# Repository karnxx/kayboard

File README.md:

# split keyboard - kayboard
https://a360.co/4jg0f7l
basically a keyboard, it can split into 3, which is a left side, a right side and a middle calculator side. so these keyboards can also join together to make 1 big keyboard via rails. 

## hardware
- uses 3  XIAO-nRF52840-SMD, one for each keyboard part. and also uses cherry mx switches.
- https://docs.google.com/spreadsheets/d/1L9tUZh8eFOhgZV8CGI-1AN47H67KgHnQl9KeM_NllnM/edit?usp=sharing

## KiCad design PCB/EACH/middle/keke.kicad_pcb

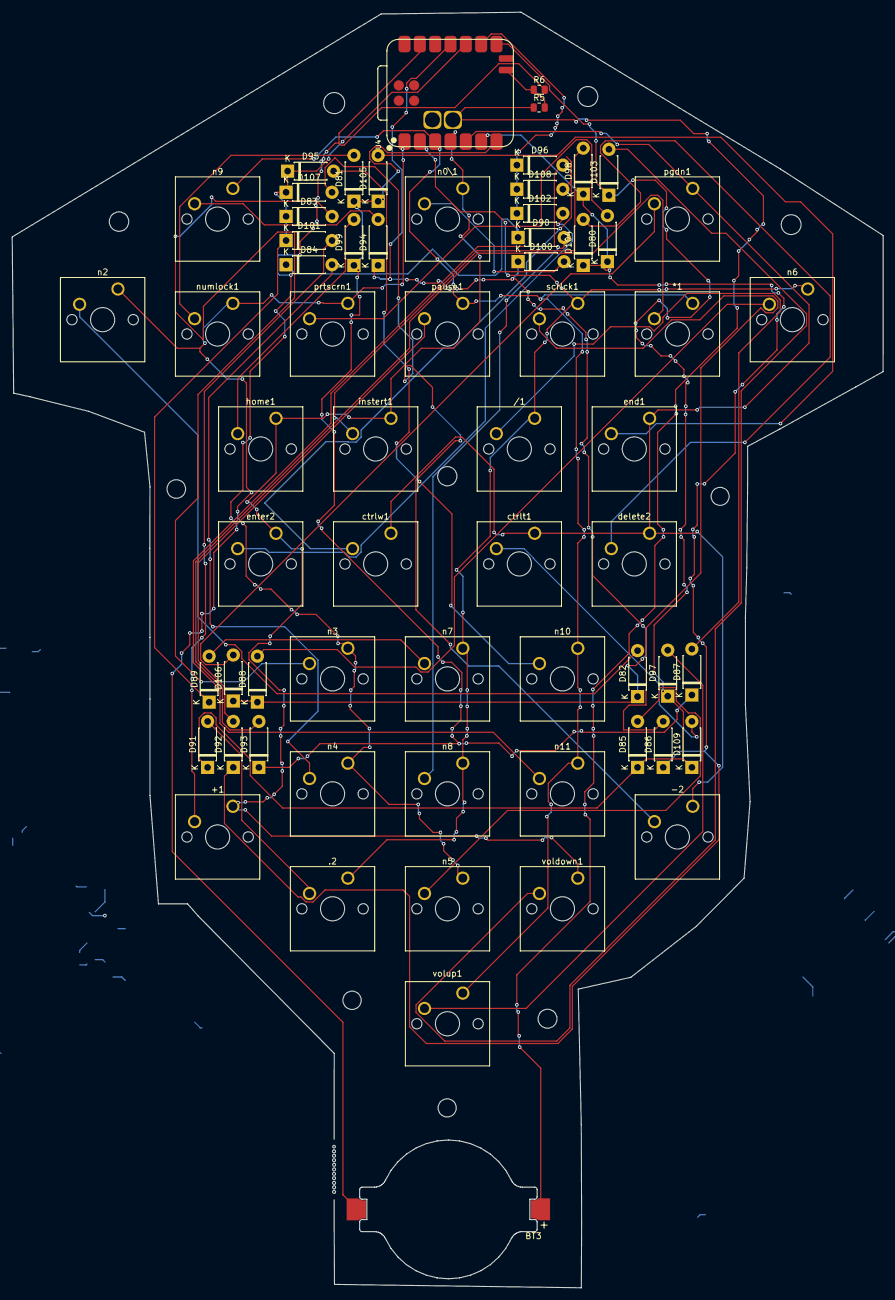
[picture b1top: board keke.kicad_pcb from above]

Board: 2 copper layers, 144.3 x 211.4 mm, 64 parts (0 on the bottom side), 44 nets.

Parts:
*1: SW_Push; SW_Cherry_MX_1.00u_PCB
+1: SW_Push; SW_Cherry_MX_1.00u_PCB
-2: SW_Push; SW_Cherry_MX_1.00u_PCB
.2: SW_Push; SW_Cherry_MX_1.00u_PCB
/1: SW_Push; SW_Cherry_MX_1.00u_PCB
BT3: Battery; BatteryHolder_Keystone_1057_1x2032
D80, D81, D82, D83, D84, D85, D86, D87, D88, D89, D90, D91, D92, D93, D94, D95, D96, D97, D98, D99, D100, D101, D102, D103, D104, D105, D106, D107, D108, D109: D; D_DO-41_SOD81_P7.62mm_Horizontal
R5, R6: R; R_0805_2012Metric
U4: XIAO-nRF52840-SMD; modified-XIAO-nRF52840-SMD
ctrlt1: SW_Push; SW_Cherry_MX_1.00u_PCB
ctrlw1: SW_Push; SW_Cherry_MX_1.00u_PCB
delete2: SW_Push; SW_Cherry_MX_1.00u_PCB
end1: SW_Push; SW_Cherry_MX_1.00u_PCB
enter2: SW_Push; SW_Cherry_MX_1.00u_PCB
home1: SW_Push; SW_Cherry_MX_1.00u_PCB
instert1: SW_Push; SW_Cherry_MX_1.00u_PCB
n0\1, n2, n3, n4, n5, n6, n7, n8, n9, n10, n11: SW_Push; SW_Cherry_MX_1.00u_PCB
numlock1: SW_Push; SW_Cherry_MX_1.00u_PCB
pause1: SW_Push; SW_Cherry_MX_1.00u_PCB
pgdn1: SW_Push; SW_Cherry_MX_1.00u_PCB
prtscrn1: SW_Push; SW_Cherry_MX_1.00u_PCB
scrlck1: SW_Push; SW_Cherry_MX_1.00u_PCB
voldown1: SW_Push; SW_Cherry_MX_1.00u_PCB
volup1: SW_Push; SW_Cherry_MX_1.00u_PCB

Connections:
/middle/VBAT3: BT3.1 (+), R5.1, U4.15 (BAT)
/middle/c0: U4.1 (P0.02_A0_D0), n2.1, n3.1, n4.1, n5.1, numlock1.1, prtscrn1.1
/middle/c1: .2.1, /1.1, U4.2 (P0.03_A1_D1), n6.1, n7.1, n8.1, scrlck1.1
/middle/c2: *1.1, U4.3 (P0.28_A2_D2), n9.1, n10.1, n11.1, pause1.1, volup1.1
/middle/c3: +1.1, U4.4 (P0.29_A3_D3), enter2.1, home1.1, instert1.1, n0\1.1, voldown1.1
/middle/c4: -2.1, U4.5 (P0.04_A4_D4_SDA), ctrlt1.1, ctrlw1.1, delete2.1, end1.1, pgdn1.1
/middle/pin: R5.2, R6.1, U4.17 (NFC1)
/middle/r0: D80.1 (K), D86.1 (K), D92.1 (K), D98.1 (K), D104.1 (K), U4.6 (P0.05_A5_D5_SCL)
/middle/r1: D81.1 (K), D87.1 (K), D93.1 (K), D99.1 (K), D105.1 (K), U4.7 (P1.11_D6_TX)
/middle/r2: D82.1 (K), D88.1 (K), D94.1 (K), D100.1 (K), D106.1 (K), U4.11 (P1.15_D10_MOSI)
/middle/r3: D83.1 (K), D89.1 (K), D95.1 (K), D101.1 (K), D107.1 (K), U4.10 (P1.14_D9_MISO)
/middle/r4: D84.1 (K), D90.1 (K), D96.1 (K), D102.1 (K), D108.1 (K), U4.9 (P1.13_D8_SCK)
/middle/r5: D85.1 (K), D91.1 (K), D97.1 (K), D103.1 (K), D109.1 (K), U4.8 (P1.12_D7_RX)
GND3: BT3.2 (-), R6.2, U4.13 (GND)
unnamed: D80.2 (A), prtscrn1.2
unnamed: D81.2 (A), numlock1.2
unnamed: D82.2 (A), n2.2
unnamed: D83.2 (A), n3.2
unnamed: D84.2 (A), n4.2
unnamed: D85.2 (A), n5.2
unnamed: D86.2 (A), scrlck1.2
unnamed: /1.2, D87.2 (A)
unnamed: D88.2 (A), n6.2
unnamed: D89.2 (A), n7.2
unnamed: D90.2 (A), n8.2
unnamed: .2.2, D91.2 (A)
unnamed: D92.2 (A), pause1.2
unnamed: *1.2, D93.2 (A)
unnamed: D94.2 (A), n9.2
unnamed: D95.2 (A), n10.2
unnamed: D96.2 (A), n11.2
unnamed: D97.2 (A), volup1.2
unnamed: D98.2 (A), instert1.2
unnamed: D99.2 (A), home1.2
unnamed: D100.2 (A), n0\1.2
unnamed: +1.2, D101.2 (A)
unnamed: D102.2 (A), enter2.2
unnamed: D103.2 (A), voldown1.2
unnamed: D104.2 (A), delete2.2
unnamed: D105.2 (A), end1.2
unnamed: D106.2 (A), pgdn1.2
unnamed: -2.2, D107.2 (A)
unnamed: D108.2 (A), ctrlw1.2
unnamed: D109.2 (A), ctrlt1.2

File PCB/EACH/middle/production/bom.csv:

Designator,Footprint,Quantity,Value,LCSC Part #
"*1, +1, -2, .2, /1, CTRLT1, CTRLW1, DELETE2, END1, ENTER2, HOME1, INSTERT1, N0\1, N10, N11, N2, N3, N4, N5, N6, N7, N8, N9, NUMLOCK1, PAUSE1, PGDN1, PRTSCRN1, SCRLCK1, VOLDOWN1, VOLUP1",SW_Cherry_MX_1.00u_PCB,30,SW_Push,
BT3,BatteryHolder_Keystone_1057_1x2032,1,Battery,
"D100, D101, D102, D103, D104, D105, D106, D107, D108, D109, D80, D81, D82, D83, D84, D85, D86, D87, D88, D89, D90, D91, D92, D93, D94, D95, D96, D97, D98, D99",D_DO-41_SOD81_P7.62mm_Horizontal,30,D,
"R5, R6",0805,2,R,
U4,modified-XIAO-nRF52840-SMD,1,XIAO-nRF52840-SMD,

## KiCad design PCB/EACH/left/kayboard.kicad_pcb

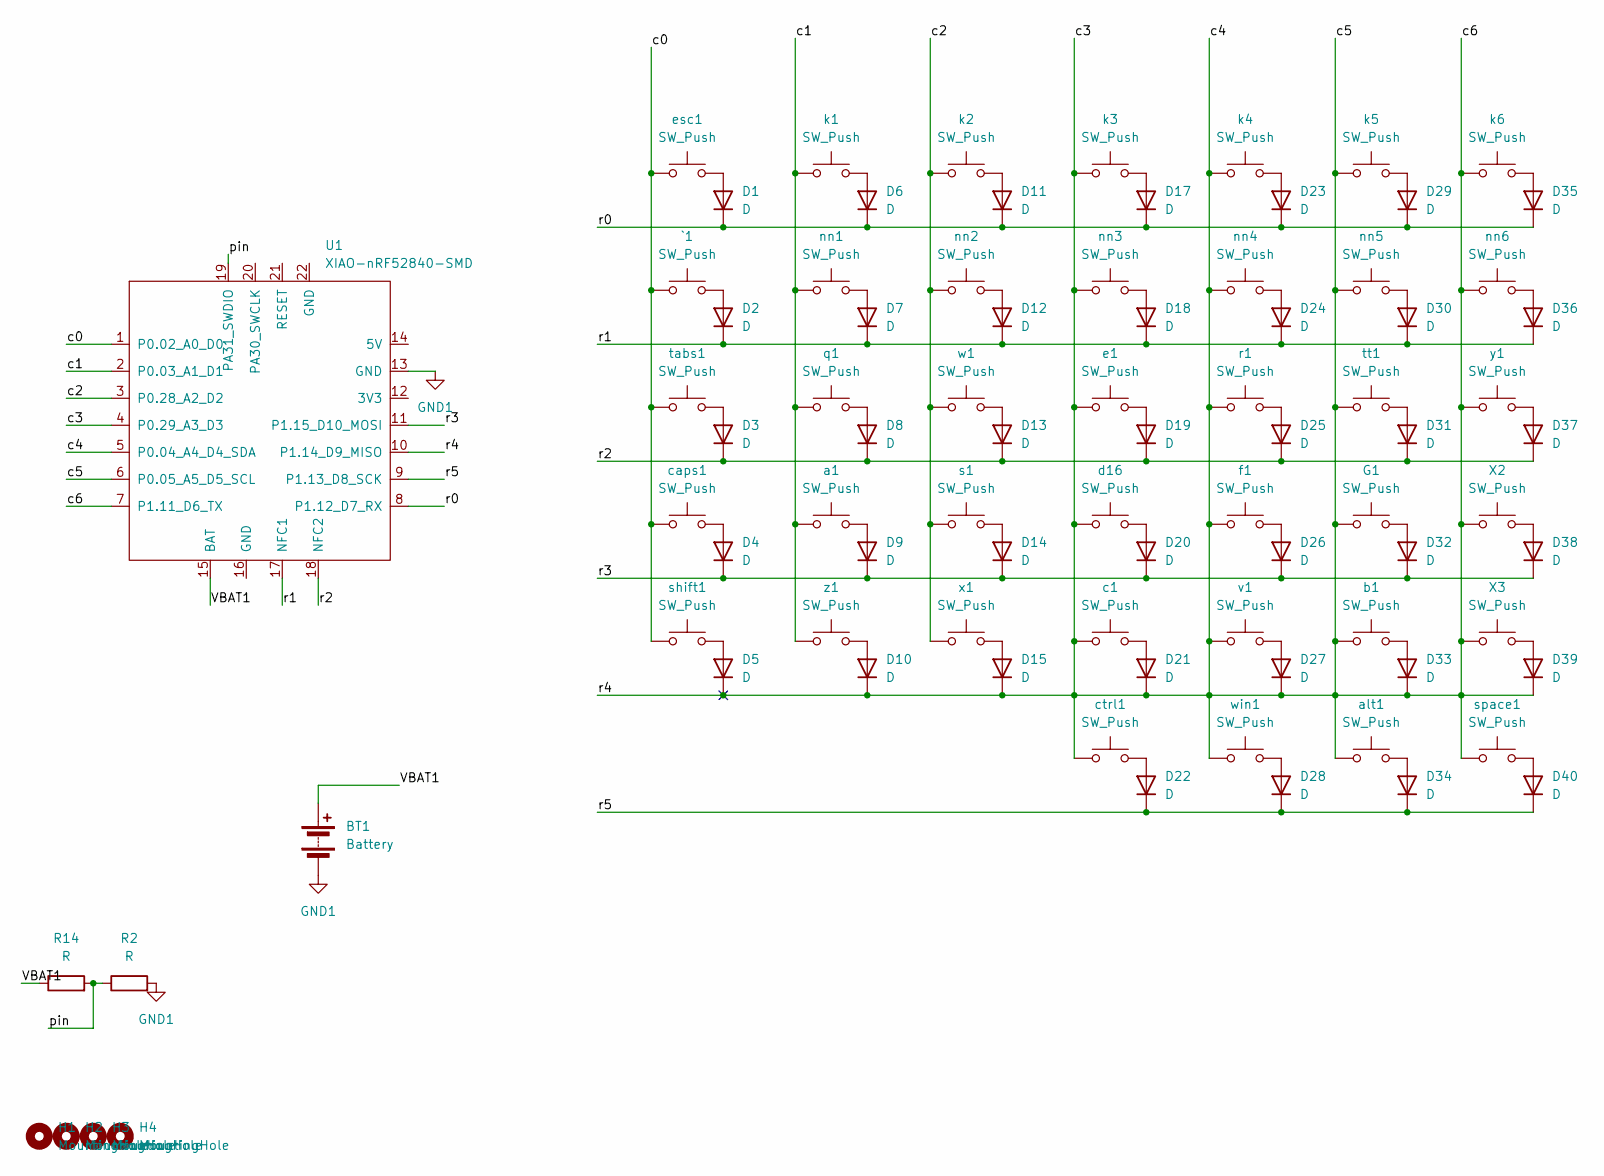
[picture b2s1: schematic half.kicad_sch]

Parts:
BT1: Battery; BatteryHolder_Keystone_1057_1x2032
D1, D2, D3, D4, D5, D6, D7, D8, D9, D10, D11, D12, D13, D14, D15, D17, D18, D19, D20, D21, D22, D23, D24, D25, D26, D27, D28, D29, D30, D31, D32, D33, D34, D35, D36, D37, D38, D39, D40: D; D_DO-41_SOD81_P7.62mm_Horizontal
G1: SW_Push; SW_Cherry_MX_1.00u_PCB
H1, H2, H3, H4: MountingHole; mouse-bite-5mm-slot
R2, R14: R; R_0805_2012Metric
U1: XIAO-nRF52840-SMD; modified-XIAO-nRF52840-SMD
X2, X3: SW_Push; SW_Cherry_MX_1.00u_PCB
`1: SW_Push; SW_Cherry_MX_1.00u_PCB
a1: SW_Push; SW_Cherry_MX_1.00u_PCB
alt1: SW_Push; SW_Cherry_MX_1.00u_PCB
b1: SW_Push; SW_Cherry_MX_1.00u_PCB
c1: SW_Push; SW_Cherry_MX_1.00u_PCB
caps1: SW_Push; SW_Cherry_MX_1.00u_PCB
ctrl1: SW_Push; SW_Cherry_MX_1.00u_PCB
d16: SW_Push; SW_Cherry_MX_1.00u_PCB
e1: SW_Push; SW_Cherry_MX_1.00u_PCB
esc1: SW_Push; SW_Cherry_MX_1.00u_PCB
f1: SW_Push; SW_Cherry_MX_1.00u_PCB
k1, k2, k3, k4, k5, k6: SW_Push; SW_Cherry_MX_1.00u_PCB
nn1, nn2, nn3, nn4, nn5, nn6: SW_Push; SW_Cherry_MX_1.00u_PCB
q1: SW_Push; SW_Cherry_MX_1.00u_PCB
r1: SW_Push; SW_Cherry_MX_1.00u_PCB
s1: SW_Push; SW_Cherry_MX_1.00u_PCB
shift1: SW_Push; SW_Cherry_MX_1.00u_PCB
space1: SW_Push; SW_Cherry_MX_1.00u_PCB
tabs1: SW_Push; SW_Cherry_MX_1.00u_PCB
tt1: SW_Push; SW_Cherry_MX_1.00u_PCB
v1: SW_Push; SW_Cherry_MX_1.00u_PCB
w1: SW_Push; SW_Cherry_MX_1.00u_PCB
win1: SW_Push; SW_Cherry_MX_1.00u_PCB
x1: SW_Push; SW_Cherry_MX_1.00u_PCB
y1: SW_Push; SW_Cherry_MX_1.00u_PCB
z1: SW_Push; SW_Cherry_MX_1.00u_PCB

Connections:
/left/VBAT1: BT1.1 (+), R14.1, U1.15 (BAT)
/left/c0: U1.1 (P0.02_A0_D0), `1.1, caps1.1, esc1.1, shift1.1, tabs1.1
/left/c1: U1.2 (P0.03_A1_D1), a1.1, k1.1, nn1.1, q1.1, z1.1
/left/c2: U1.3 (P0.28_A2_D2), k2.1, nn2.1, s1.1, w1.1, x1.1
/left/c3: D5.1 (K), D10.1 (K), D15.1 (K), D21.1 (K), D27.1 (K), D33.1 (K), D39.1 (K), G1.1, U1.4 (P0.29_A3_D3), U1.5 (P0.04_A4_D4_SDA), U1.6 (P0.05_A5_D5_SCL), U1.7 (P1.11_D6_TX), U1.10 (P1.14_D9_MISO), X2.1, X3.1, alt1.1, b1.1, c1.1, ctrl1.1, d16.1, e1.1, f1.1, k3.1, k4.1, k5.1, k6.1, nn3.1, nn4.1, nn5.1, nn6.1, r1.1, space1.1, tt1.1, v1.1, win1.1, y1.1
/left/pin: R2.1, R14.2, U1.19 (PA31_SWDIO)
/left/r0: D1.1 (K), D6.1 (K), D11.1 (K), D17.1 (K), D23.1 (K), D29.1 (K), D35.1 (K), U1.8 (P1.12_D7_RX)
/left/r1: D2.1 (K), D7.1 (K), D12.1 (K), D18.1 (K), D24.1 (K), D30.1 (K), D36.1 (K), U1.17 (NFC1)
/left/r2: D3.1 (K), D8.1 (K), D13.1 (K), D19.1 (K), D25.1 (K), D31.1 (K), D37.1 (K), U1.18 (NFC2)
/left/r3: D4.1 (K), D9.1 (K), D14.1 (K), D20.1 (K), D26.1 (K), D32.1 (K), D38.1 (K), U1.11 (P1.15_D10_MOSI)
/left/r5: D22.1 (K), D28.1 (K), D34.1 (K), D40.1 (K), U1.9 (P1.13_D8_SCK)
GND1: BT1.2 (-), R2.2, U1.13 (GND)
unnamed: D1.2 (A), esc1.2
unnamed: D2.2 (A), `1.2
unnamed: D3.2 (A), tabs1.2
unnamed: D4.2 (A), caps1.2
unnamed: D5.2 (A), shift1.2
unnamed: D6.2 (A), k1.2
unnamed: D7.2 (A), nn1.2
unnamed: D8.2 (A), q1.2
unnamed: D9.2 (A), a1.2
unnamed: D10.2 (A), z1.2
unnamed: D11.2 (A), k2.2
unnamed: D12.2 (A), nn2.2
unnamed: D13.2 (A), w1.2
unnamed: D14.2 (A), s1.2
unnamed: D15.2 (A), x1.2
unnamed: D17.2 (A), k3.2
unnamed: D18.2 (A), nn3.2
unnamed: D19.2 (A), e1.2
unnamed: D20.2 (A), d16.2
unnamed: D21.2 (A), c1.2
unnamed: D22.2 (A), ctrl1.2
unnamed: D23.2 (A), k4.2
unnamed: D24.2 (A), nn4.2
unnamed: D25.2 (A), r1.2
unnamed: D26.2 (A), f1.2
unnamed: D27.2 (A), v1.2
unnamed: D28.2 (A), win1.2
unnamed: D29.2 (A), k5.2
unnamed: D30.2 (A), nn5.2
unnamed: D31.2 (A), tt1.2
unnamed: D32.2 (A), G1.2
unnamed: D33.2 (A), b1.2
unnamed: D34.2 (A), alt1.2
unnamed: D35.2 (A), k6.2
unnamed: D36.2 (A), nn6.2
unnamed: D37.2 (A), y1.2
unnamed: D38.2 (A), X2.2
unnamed: D39.2 (A), X3.2
unnamed: D40.2 (A), space1.2

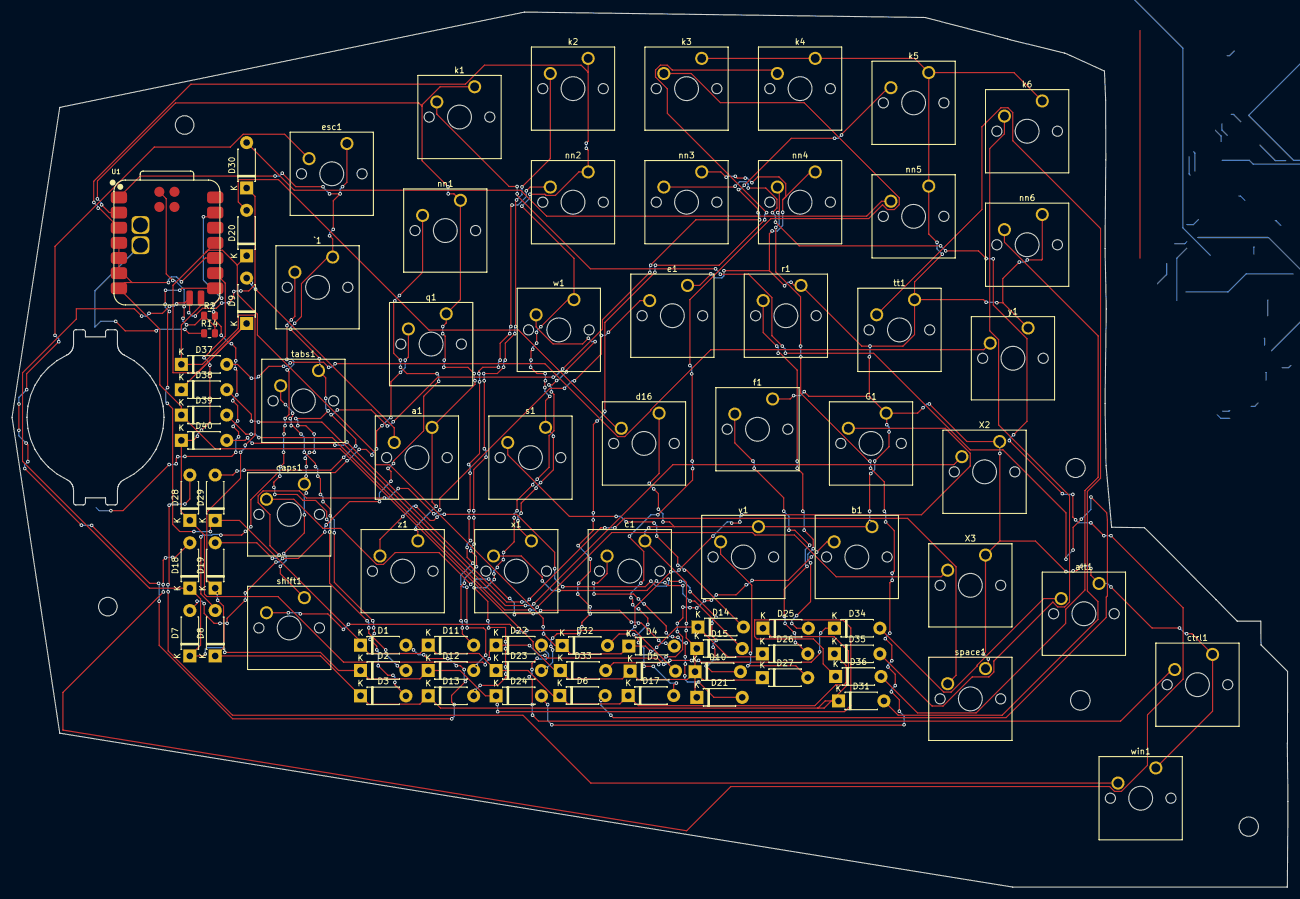
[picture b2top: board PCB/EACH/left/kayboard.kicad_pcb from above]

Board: 2 copper layers, 214.1 x 146.8 mm, 82 parts (1 on the bottom side), 51 nets.

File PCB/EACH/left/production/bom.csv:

Designator,Footprint,Quantity,Value,LCSC Part #
"A1, ALT1, B1, C1, CAPS1, CTRL1, D16, E1, ESC1, F1, G1, K1, K2, K3, K4, K5, K6, NN1, NN2, NN3, NN4, NN5, NN6, Q1, R1, S1, SHIFT1, SPACE1, TABS1, TT1, V1, W1, WIN1, X1, X2, X3, Y1, Z1, `1",SW_Cherry_MX_1.00u_PCB,39,SW_Push,
BT1,BatteryHolder_Keystone_1057_1x2032,1,Battery,
"D1, D10, D11, D12, D13, D14, D15, D17, D18, D19, D2, D20, D21, D22, D23, D24, D25, D26, D27, D28, D29, D3, D30, D31, D32, D33, D34, D35, D36, D37, D38, D39, D4, D40, D5, D6, D7, D8, D9",D_DO-41_SOD81_P7.62mm_Horizontal,39,D,
"R14, R2",0805,2,R,
U1,modified-XIAO-nRF52840-SMD,1,XIAO-nRF52840-SMD,

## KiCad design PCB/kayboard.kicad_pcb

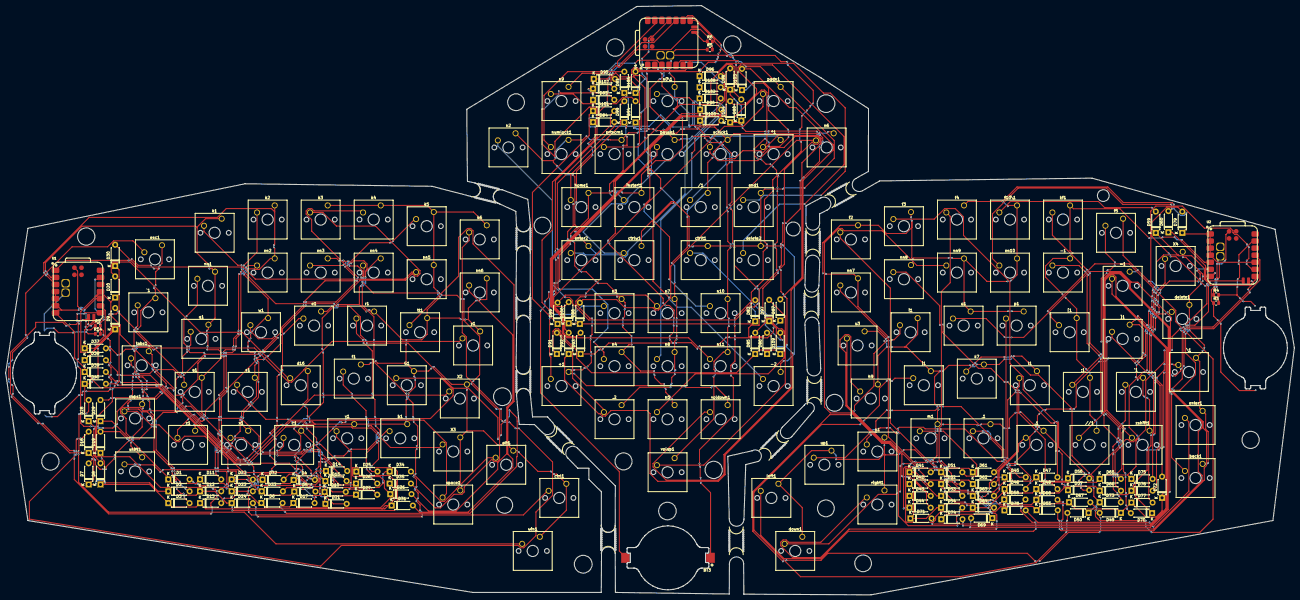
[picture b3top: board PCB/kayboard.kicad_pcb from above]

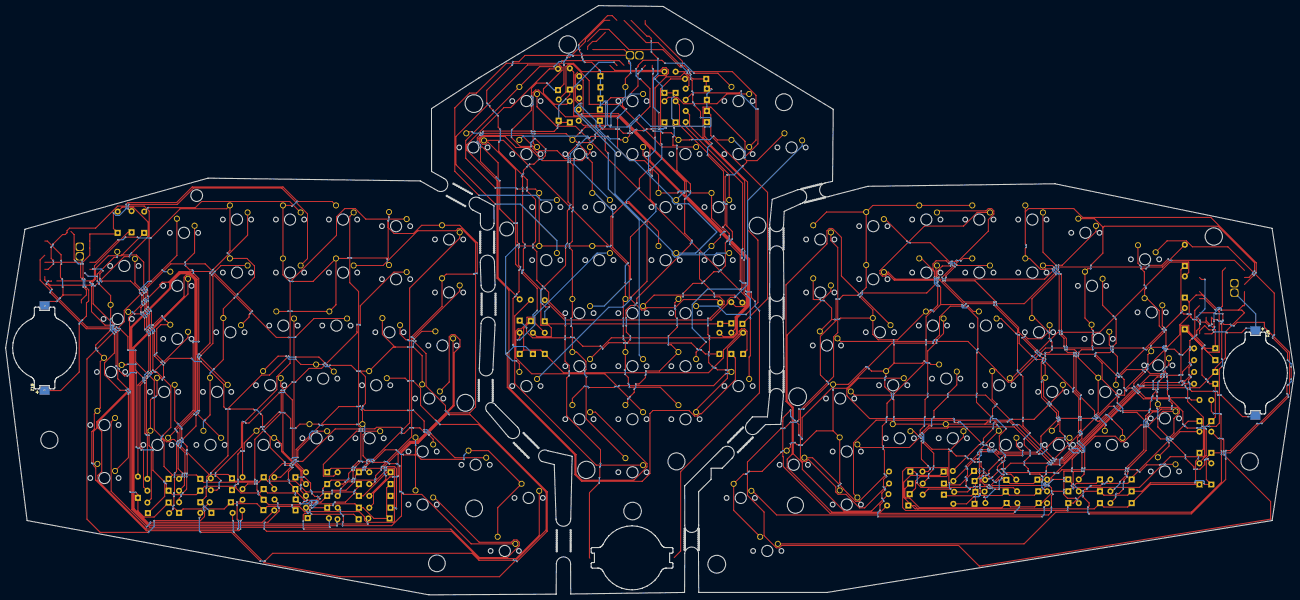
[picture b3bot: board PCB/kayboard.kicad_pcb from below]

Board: 2 copper layers, 463.0 x 211.7 mm, 240 parts (2 on the bottom side), 146 nets.

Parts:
'1: SW_Push; SW_Cherry_MX_1.00u_PCB
*1: SW_Push; SW_Cherry_MX_1.00u_PCB
+1: SW_Push; SW_Cherry_MX_1.00u_PCB
,1: SW_Push; SW_Cherry_MX_1.00u_PCB
-1, -2: SW_Push; SW_Cherry_MX_1.00u_PCB
.1, .2: SW_Push; SW_Cherry_MX_1.00u_PCB
/1: SW_Push; SW_Cherry_MX_1.00u_PCB
//1: SW_Push; SW_Cherry_MX_1.00u_PCB
;1: SW_Push; SW_Cherry_MX_1.00u_PCB
=1: SW_Push; SW_Cherry_MX_1.00u_PCB
BT1, BT2, BT3: Battery; BatteryHolder_Keystone_1057_1x2032
D1, D2, D3, D4, D5, D6, D7, D8, D9, D10, D11, D12, D13, D14, D15, D17, D18, D19, D20, D21, D22, D23, D24, D25, D26, D27, D28, D29, D30, D31, D32, D33, D34, D35, D36, D37, D38, D39, D40, D41, D42, D43, D44, D45, D46, D47, D48, D49, D50, D51, D52, D53, D54, D55, D56, D57, D58, D59, D60, D61, D62, D63, D64, D65, D66, D67, D68, D69, D70, D71, D72, D73, D74, D75, D76, D77, D78, D79, D80, D81, D82, D83, D84, D85, D86, D87, D88, D89, D90, D91, D92, D93, D94, D95, D96, D97, D98, D99, D100, D101, D102, D103, D104, D105, D106, D107, D108, D109: D; D_DO-41_SOD81_P7.62mm_Horizontal
G1: SW_Push; SW_Cherry_MX_1.00u_PCB
H1, H2, H3, H4, H5, H6, H7, H8, H10, H11, H12, H13: MountingHole; mouse-bite-5mm-slot
R2, R3, R4, R5, R6, R14: R; R_0805_2012Metric
U1, U2, U4: XIAO-nRF52840-SMD; modified-XIAO-nRF52840-SMD
X2, X3, X4: SW_Push; SW_Cherry_MX_1.00u_PCB
[1: SW_Push; SW_Cherry_MX_1.00u_PCB
\1: SW_Push; SW_Cherry_MX_1.00u_PCB
]1: SW_Push; SW_Cherry_MX_1.00u_PCB
`1: SW_Push; SW_Cherry_MX_1.00u_PCB
a1: SW_Push; SW_Cherry_MX_1.00u_PCB
alt1: SW_Push; SW_Cherry_MX_1.00u_PCB
b1: SW_Push; SW_Cherry_MX_1.00u_PCB
back1: SW_Push; SW_Cherry_MX_1.00u_PCB
c1: SW_Push; SW_Cherry_MX_1.00u_PCB
caps1: SW_Push; SW_Cherry_MX_1.00u_PCB
ctrl1: SW_Push; SW_Cherry_MX_1.00u_PCB
ctrlt1: SW_Push; SW_Cherry_MX_1.00u_PCB
ctrlw1: SW_Push; SW_Cherry_MX_1.00u_PCB
d16: SW_Push; SW_Cherry_MX_1.00u_PCB
delete1, delete2: SW_Push; SW_Cherry_MX_1.00u_PCB
down1: SW_Push; SW_Cherry_MX_1.00u_PCB
e1: SW_Push; SW_Cherry_MX_1.00u_PCB
end1: SW_Push; SW_Cherry_MX_1.00u_PCB
enter1, enter2: SW_Push; SW_Cherry_MX_1.00u_PCB
esc1: SW_Push; SW_Cherry_MX_1.00u_PCB
f1, f2, f3, f4, f5, f10\1: SW_Push; SW_Cherry_MX_1.00u_PCB
h9: SW_Push; SW_Cherry_MX_1.00u_PCB
home1: SW_Push; SW_Cherry_MX_1.00u_PCB
i1: SW_Push; SW_Cherry_MX_1.00u_PCB
instert1: SW_Push; SW_Cherry_MX_1.00u_PCB
j1: SW_Push; SW_Cherry_MX_1.00u_PCB
k1, k2, k3, k4, k5, k6, k7: SW_Push; SW_Cherry_MX_1.00u_PCB
kf1: SW_Push; SW_Cherry_MX_1.00u_PCB
l1: SW_Push; SW_Cherry_MX_1.00u_PCB
left1: SW_Push; SW_Cherry_MX_1.00u_PCB
m1: SW_Push; SW_Cherry_MX_1.00u_PCB
n0\1, n1, n2, n3, n4, n5, n6, n7, n8, n9, n10, n11: SW_Push; SW_Cherry_MX_1.00u_PCB
nn1, nn2, nn3, nn4, nn5, nn6, nn7, nn8, nn9, nn10: SW_Push; SW_Cherry_MX_1.00u_PCB
numlock1: SW_Push; SW_Cherry_MX_1.00u_PCB
o1: SW_Push; SW_Cherry_MX_1.00u_PCB
p1: SW_Push; SW_Cherry_MX_1.00u_PCB
pause1: SW_Push; SW_Cherry_MX_1.00u_PCB
pgdn1: SW_Push; SW_Cherry_MX_1.00u_PCB
prtscrn1: SW_Push; SW_Cherry_MX_1.00u_PCB
q1: SW_Push; SW_Cherry_MX_1.00u_PCB
r1: SW_Push; SW_Cherry_MX_1.00u_PCB
right1: SW_Push; SW_Cherry_MX_1.00u_PCB
s1: SW_Push; SW_Cherry_MX_1.00u_PCB
scrlck1: SW_Push; SW_Cherry_MX_1.00u_PCB
shift1: SW_Push; SW_Cherry_MX_1.00u_PCB
space1: SW_Push; SW_Cherry_MX_1.00u_PCB
tabs1: SW_Push; SW_Cherry_MX_1.00u_PCB
tt1: SW_Push; SW_Cherry_MX_1.00u_PCB
u3: SW_Push; SW_Cherry_MX_1.00u_PCB
up1: SW_Push; SW_Cherry_MX_1.00u_PCB
v1: SW_Push; SW_Cherry_MX_1.00u_PCB
voldown1: SW_Push; SW_Cherry_MX_1.00u_PCB
volup1: SW_Push; SW_Cherry_MX_1.00u_PCB
w1: SW_Push; SW_Cherry_MX_1.00u_PCB
win1: SW_Push; SW_Cherry_MX_1.00u_PCB
x1: SW_Push; SW_Cherry_MX_1.00u_PCB
y1: SW_Push; SW_Cherry_MX_1.00u_PCB
z1: SW_Push; SW_Cherry_MX_1.00u_PCB
zshift1: SW_Push; SW_Cherry_MX_1.00u_PCB

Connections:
/left/VBAT1: BT1.1 (+), R14.1, U1.15 (BAT)
/left/c0: U1.1 (P0.02_A0_D0), `1.1, caps1.1, esc1.1, shift1.1, tabs1.1
/left/c1: U1.2 (P0.03_A1_D1), a1.1, k1.1, nn1.1, q1.1, z1.1
/left/c2: U1.3 (P0.28_A2_D2), k2.1, nn2.1, s1.1, w1.1, x1.1
/left/c3: D5.1 (K), D10.1 (K), D15.1 (K), D21.1 (K), D27.1 (K), D33.1 (K), D39.1 (K), G1.1, U1.4 (P0.29_A3_D3), U1.5 (P0.04_A4_D4_SDA), U1.6 (P0.05_A5_D5_SCL), U1.7 (P1.11_D6_TX), U1.10 (P1.14_D9_MISO), X2.1, X3.1, alt1.1, b1.1, c1.1, ctrl1.1, d16.1, e1.1, f1.1, k3.1, k4.1, k5.1, k6.1, nn3.1, nn4.1, nn5.1, nn6.1, r1.1, space1.1, tt1.1, v1.1, win1.1, y1.1
/left/pin: R2.1, R14.2, U1.19 (PA31_SWDIO)
/left/r0: D1.1 (K), D6.1 (K), D11.1 (K), D17.1 (K), D23.1 (K), D29.1 (K), D35.1 (K), U1.8 (P1.12_D7_RX)
/left/r1: D2.1 (K), D7.1 (K), D12.1 (K), D18.1 (K), D24.1 (K), D30.1 (K), D36.1 (K), U1.17 (NFC1)
/left/r2: D3.1 (K), D8.1 (K), D13.1 (K), D19.1 (K), D25.1 (K), D31.1 (K), D37.1 (K), U1.18 (NFC2)
/left/r3: D4.1 (K), D9.1 (K), D14.1 (K), D20.1 (K), D26.1 (K), D32.1 (K), D38.1 (K), U1.11 (P1.15_D10_MOSI)
/left/r5: D22.1 (K), D28.1 (K), D34.1 (K), D40.1 (K), U1.9 (P1.13_D8_SCK)
/middle/VBAT3: BT3.1 (+), R5.1, U4.15 (BAT)
/middle/c0: U4.1 (P0.02_A0_D0), n2.1, n3.1, n4.1, n5.1, numlock1.1, prtscrn1.1
/middle/c1: .2.1, /1.1, U4.2 (P0.03_A1_D1), n6.1, n7.1, n8.1, scrlck1.1
/middle/c2: *1.1, U4.3 (P0.28_A2_D2), n9.1, n10.1, n11.1, pause1.1, volup1.1
/middle/c3: +1.1, U4.4 (P0.29_A3_D3), enter2.1, home1.1, instert1.1, n0\1.1, voldown1.1
/middle/c4: -2.1, U4.5 (P0.04_A4_D4_SDA), ctrlt1.1, ctrlw1.1, delete2.1, end1.1, pgdn1.1
/middle/pin: R5.2, R6.1, U4.17 (NFC1)
/middle/r0: D80.1 (K), D86.1 (K), D92.1 (K), D98.1 (K), D104.1 (K), U4.6 (P0.05_A5_D5_SCL)
/middle/r1: D81.1 (K), D87.1 (K), D93.1 (K), D99.1 (K), D105.1 (K), U4.7 (P1.11_D6_TX)
/middle/r2: D82.1 (K), D88.1 (K), D94.1 (K), D100.1 (K), D106.1 (K), U4.11 (P1.15_D10_MOSI)
/middle/r3: D83.1 (K), D89.1 (K), D95.1 (K), D101.1 (K), D107.1 (K), U4.10 (P1.14_D9_MISO)
/middle/r4: D84.1 (K), D90.1 (K), D96.1 (K), D102.1 (K), D108.1 (K), U4.9 (P1.13_D8_SCK)
/middle/r5: D85.1 (K), D91.1 (K), D97.1 (K), D103.1 (K), D109.1 (K), U4.8 (P1.12_D7_RX)
/right/VBAT2: BT2.1 (+), R3.1, U2.15 (BAT)
/right/c0: ,1.1, .1.1, D45.1 (K), D51.1 (K), D57.1 (K), D63.1 (K), D69.1 (K), D74.1 (K), D79.1 (K), U2.1 (P0.02_A0_D0), U2.2 (P0.03_A1_D1), U2.3 (P0.28_A2_D2), U2.4 (P0.29_A3_D3), U2.10 (P1.14_D9_MISO), down1.1, f2.1, f3.1, f4.1, f10\1.1, h9.1, i1.1, j1.1, k7.1, l1.1, left1.1, m1.1, n1.1, nn7.1, nn8.1, nn9.1, nn10.1, o1.1, p1.1, right1.1, u3.1, up1.1
/right/c4: -1.1, //1.1, ;1.1, U2.5 (P0.04_A4_D4_SDA), [1.1, kf1.1
/right/c5: '1.1, =1.1, U2.6 (P0.05_A5_D5_SCL), ]1.1, f5.1, zshift1.1
/right/c6: U2.7 (P1.11_D6_TX), X4.1, \1.1, back1.1, delete1.1, enter1.1
/right/pin: R3.2, R4.1, U2.19 (PA31_SWDIO)
/right/r0: D41.1 (K), D47.1 (K), D53.1 (K), D59.1 (K), D65.1 (K), D70.1 (K), D75.1 (K), U2.8 (P1.12_D7_RX)
/right/r1: D42.1 (K), D48.1 (K), D54.1 (K), D60.1 (K), D66.1 (K), D71.1 (K), D76.1 (K), U2.17 (NFC1)
/right/r2: D43.1 (K), D49.1 (K), D55.1 (K), D61.1 (K), D67.1 (K), D72.1 (K), D77.1 (K), U2.18 (NFC2)
/right/r3: D44.1 (K), D50.1 (K), D56.1 (K), D62.1 (K), D68.1 (K), D73.1 (K), D78.1 (K), U2.11 (P1.15_D10_MOSI)
/right/r5: D46.1 (K), D52.1 (K), D58.1 (K), D64.1 (K), U2.9 (P1.13_D8_SCK)
GND1: BT1.2 (-), R2.2, U1.13 (GND)
GND2: BT2.2 (-), R4.2, U2.13 (GND)
GND3: BT3.2 (-), R6.2, U4.13 (GND)
unnamed: D1.2 (A), esc1.2
unnamed: D2.2 (A), `1.2
unnamed: D3.2 (A), tabs1.2
unnamed: D4.2 (A), caps1.2
unnamed: D5.2 (A), shift1.2
unnamed: D6.2 (A), k1.2
unnamed: D7.2 (A), nn1.2
unnamed: D8.2 (A), q1.2
unnamed: D9.2 (A), a1.2
unnamed: D10.2 (A), z1.2
unnamed: D11.2 (A), k2.2
unnamed: D12.2 (A), nn2.2
unnamed: D13.2 (A), w1.2
unnamed: D14.2 (A), s1.2
unnamed: D15.2 (A), x1.2
unnamed: D17.2 (A), k3.2
unnamed: D18.2 (A), nn3.2
unnamed: D19.2 (A), e1.2
unnamed: D20.2 (A), d16.2
unnamed: D21.2 (A), c1.2
unnamed: D22.2 (A), ctrl1.2
unnamed: D23.2 (A), k4.2
unnamed: D24.2 (A), nn4.2
unnamed: D25.2 (A), r1.2
unnamed: D26.2 (A), f1.2
unnamed: D27.2 (A), v1.2
unnamed: D28.2 (A), win1.2
unnamed: D29.2 (A), k5.2
unnamed: D30.2 (A), nn5.2
unnamed: D31.2 (A), tt1.2
unnamed: D32.2 (A), G1.2
unnamed: D33.2 (A), b1.2
unnamed: D34.2 (A), alt1.2
unnamed: D35.2 (A), k6.2
unnamed: D36.2 (A), nn6.2
unnamed: D37.2 (A), y1.2
unnamed: D38.2 (A), X2.2
unnamed: D39.2 (A), X3.2
unnamed: D40.2 (A), space1.2
unnamed: D41.2 (A), f2.2
unnamed: D42.2 (A), nn7.2
unnamed: D43.2 (A), u3.2
unnamed: D44.2 (A), h9.2
unnamed: D45.2 (A), n1.2
unnamed: D46.2 (A), up1.2
unnamed: D47.2 (A), f3.2
unnamed: D48.2 (A), nn8.2
unnamed: D49.2 (A), i1.2
unnamed: D50.2 (A), j1.2
unnamed: D51.2 (A), m1.2
unnamed: D52.2 (A), down1.2
unnamed: D53.2 (A), f4.2
unnamed: D54.2 (A), nn9.2
unnamed: D55.2 (A), o1.2
unnamed: D56.2 (A), k7.2
unnamed: ,1.2, D57.2 (A)
unnamed: D58.2 (A), left1.2
unnamed: D59.2 (A), f10\1.2
unnamed: D60.2 (A), nn10.2
unnamed: D61.2 (A), p1.2
unnamed: D62.2 (A), l1.2
unnamed: .1.2, D63.2 (A)
unnamed: D64.2 (A), right1.2
unnamed: D65.2 (A), kf1.2
unnamed: -1.2, D66.2 (A)
unnamed: D67.2 (A), [1.2
unnamed: ;1.2, D68.2 (A)
unnamed: //1.2, D69.2 (A)
unnamed: D70.2 (A), f5.2
unnamed: =1.2, D71.2 (A)
unnamed: D72.2 (A), ]1.2
unnamed: '1.2, D73.2 (A)
unnamed: D74.2 (A), zshift1.2
unnamed: D75.2 (A), X4.2
unnamed: D76.2 (A), delete1.2
unnamed: D77.2 (A), \1.2
unnamed: D78.2 (A), enter1.2
unnamed: D79.2 (A), back1.2
unnamed: D80.2 (A), prtscrn1.2
unnamed: D81.2 (A), numlock1.2
unnamed: D82.2 (A), n2.2
unnamed: D83.2 (A), n3.2
unnamed: D84.2 (A), n4.2
unnamed: D85.2 (A), n5.2
unnamed: D86.2 (A), scrlck1.2
unnamed: /1.2, D87.2 (A)
unnamed: D88.2 (A), n6.2
unnamed: D89.2 (A), n7.2
unnamed: D90.2 (A), n8.2
unnamed: .2.2, D91.2 (A)
unnamed: D92.2 (A), pause1.2
unnamed: *1.2, D93.2 (A)
unnamed: D94.2 (A), n9.2
unnamed: D95.2 (A), n10.2
unnamed: D96.2 (A), n11.2
unnamed: D97.2 (A), volup1.2
unnamed: D98.2 (A), instert1.2
unnamed: D99.2 (A), home1.2
unnamed: D100.2 (A), n0\1.2
unnamed: +1.2, D101.2 (A)
unnamed: D102.2 (A), enter2.2
unnamed: D103.2 (A), voldown1.2
unnamed: D104.2 (A), delete2.2
unnamed: D105.2 (A), end1.2
unnamed: D106.2 (A), pgdn1.2
unnamed: -2.2, D107.2 (A)
unnamed: D108.2 (A), ctrlw1.2
unnamed: D109.2 (A), ctrlt1.2

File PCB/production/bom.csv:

Designator,Footprint,Quantity,Value,LCSC Part #
"'1, *1, +1, ,1, -1, -2, .1, .2, //1, /1, ;1, =1, A1, ALT1, B1, BACK1, C1, CAPS1, CTRL1, CTRLT1, CTRLW1, D16, DELETE1, DELETE2, DOWN1, E1, END1, ENTER1, ENTER2, ESC1, F1, F10\1, F2, F3, F4, F5, G1, H9, HOME1, I1, INSTERT1, J1, K1, K2, K3, K4, K5, K6, K7, KF1, L1, LEFT1, M1, N0\1, N1, N10, N11, N2, N3, N4, N5, N6, N7, N8, N9, NN1, NN10, NN2, NN3, NN4, NN5, NN6, NN7, NN8, NN9, NUMLOCK1, O1, P1, PAUSE1, PGDN1, PRTSCRN1, Q1, R1, RIGHT1, S1, SCRLCK1, SHIFT1, SPACE1, TABS1, TT1, U3, UP1, V1, VOLDOWN1, VOLUP1, W1, WIN1, X1, X2, X3, X4, Y1, Z1, ZSHIFT1, [1, \1, ]1, `1",SW_Cherry_MX_1.00u_PCB,108,SW_Push,
"BT1, BT2, BT3",BatteryHolder_Keystone_1057_1x2032,3,Battery,
"D1, D10, D100, D101, D102, D103, D104, D105, D106, D107, D108, D109, D11, D12, D13, D14, D15, D17, D18, D19, D2, D20, D21, D22, D23, D24, D25, D26, D27, D28, D29, D3, D30, D31, D32, D33, D34, D35, D36, D37, D38, D39, D4, D40, D41, D42, D43, D44, D45, D46, D47, D48, D49, D5, D50, D51, D52, D53, D54, D55, D56, D57, D58, D59, D6, D60, D61, D62, D63, D64, D65, D66, D67, D68, D69, D7, D70, D71, D72, D73, D74, D75, D76, D77, D78, D79, D8, D80, D81, D82, D83, D84, D85, D86, D87, D88, D89, D9, D90, D91, D92, D93, D94, D95, D96, D97, D98, D99",D_DO-41_SOD81_P7.62mm_Horizontal,108,D,
"R14, R2, R3, R4, R5, R6",0805,6,R,
"U1, U2, U4",modified-XIAO-nRF52840-SMD,3,XIAO-nRF52840-SMD,

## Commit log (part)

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2025-12-08 dddddd
2025-12-19 Create README.md for split keyboard project
    Added a README.md file describing the split keyboard.
2025-12-19 Enhance README with hardware specifications and costs
    Added hardware component details and pricing to README.
